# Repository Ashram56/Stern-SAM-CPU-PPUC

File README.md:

# Stern SAM CPU PPUC

A replacement CPU board for the Stern SAM pinball platform. A Raspberry Pi runs the original game ROM under PinMAME
through the [PPUC](https://github.com/PPUC) stack. An RP2354B on the same board drives the original IO power board bus (J1)
with its PIO, reads the switch matrix, dedicated switches and DIP switches, and can scan the original DMD.

- [docs/ARCHITECTURE.md](docs/ARCHITECTURE.md): architecture, bus timing, pin budget, safety, and open questions.
- [docs/reference/](docs/reference/): Stern SAM manual extracts (IO power driver and CPU/Sound board schematics, backbox,
  playfield, cabinet and coin door wiring).

Background:
- [Tron-Legacy-LE-ROM-Decryption/io/bus](https://github.com/Ashram56/Tron-Legacy-LE-ROM-Decryption/tree/main/io/bus):
  the CPU to IO board bus as the SAM ROM drives it.
- [Stern-SAM-Databus-Analysis](https://github.com/Ashram56/Stern-SAM-Databus-Analysis): J1 pinout and IO board schematic notes.

## Licence

- Firmware and software: GNU GPL v3 ([LICENSE](LICENSE)), matching PPUC.
- Hardware design files: CERN Open Hardware Licence v2, strongly reciprocal ([LICENSE-HARDWARE](LICENSE-HARDWARE)).
- The manual extracts in `docs/reference/` are Stern Pinball's material, kept for reference, and are not covered by
  either licence.

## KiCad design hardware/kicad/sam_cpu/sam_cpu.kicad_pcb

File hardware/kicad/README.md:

# SAM CPU replacement board: KiCad project

Draft 0.2 of the schematic, drawn from [`docs/ARCHITECTURE.md`](../../docs/ARCHITECTURE.md). The PCB placement draft is described in [`PCB.md`](PCB.md).
Licence: CERN-OHL-S v2 (see [`LICENSE-HARDWARE`](../../LICENSE-HARDWARE)).

- `sam_cpu/`: the KiCad 10 project (10.0 file format). Open `sam_cpu.kicad_pro` in KiCad 10. All symbols come from
  the standard KiCad 10 libraries and are embedded in the sheets, so no project library is needed.
- `sam_cpu/sam_cpu.pdf`: the sheets exported to PDF, for reading without KiCad.
- `tools/`: the Python scripts that generated this draft (see the end of this file).

## Sheets

Every connection is drawn as a wire. Each connector sits on the same page as the parts that drive or read it.
Signals that go to another page use global labels, and each label shows the page numbers where the signal
continues, in square brackets.

| Page | Sheet | Content | Architecture doc |
|---|---|---|---|
| 2 | Power | J11 (original connector: +5 V, ground, 12 V on pin 6), J17 external +5 V, ideal-diode mux with external priority, J23 external +12 V and J11 pin 6 through an ideal-diode OR (external priority) to the +12 V rail (polyfuse + TVS), TPS54302 buck for the Pi 5 V (a 3-pin header with one shunt picks board +5 V, buck or none for a Jetson), NCP1117 3.3 V (ceramic-stable), +4.5 V switch supply, ADC supply monitors, rail test points | 9.3 |
| 3 | MCU and Pi | RP2354B, crystal, core regulator parts, TPS3808 reset supervisor, RESET / BOOTSEL buttons, status LED, J21 Raspberry Pi 4 40-pin header (UART0, SPI0, I2S, RUN, BOOTSEL, IRQ) (no USB: the Pi flashes the RP2354B over SWD on J21 pins 18 / 22, GPIO24 / GPIO25), U25 DS3231MZ real-time clock on the Pi I2C1 with a CR2032 (BT1) | 4.2, 9.1, 9.2 |
| 4 | IO bus | J9 to IO board J1: SN74LVC8T245 data, 74AHCT541 address + IOSTB, 2N7002 open-drain NBRESET, 33 R series resistor packs | 3.1, 3.2 |
| 5 | Switch columns | 74HC595 + 8 MMBT3904 strobe drivers, J1 switch columns | 5.3, 5.4 |
| 6 | Switch rows 1-8 | J6, 8 returns: diode, 1 k to +4.5 V, 220 R + 100 nF, LM339 against 2.25 V (copy of the original), 74HC165, VREF divider | 5.2, 5.3 |
| 7 | Switch rows 9-16 | J12, same circuit, 74HC165 | 5.2, 5.3 |
| 8 | Dedicated switches 1-16 | J2, J3, input filters, 2 x 74HC165, coin door memory protect | 5.2, 5.3 |
| 9 | Dedicated switches 17-24 | J13, input filters, 74HC165 (DIP block removed) | 5.2, 5.3 |
| 10 | (removed) | GI dimmer sheet removed in the second alternative | 10.2 |
| 11 | Audio | PCM5102A DAC from Pi I2S; U23 TDA7297 bridge amplifier for left / right (J10, J22); (L + R) / 2 110 Hz low-pass (OPA1678) into U24 TDA7297 for the subwoofer (J24); all on +12 V; software mute | 8 |
| 12 | Switch chain extensions | U30 7th 74HC165 (coin door memory protect); U31 extra 74HC595 first in the strobe chain (LED_STATUS, GI_SPARE). File name `dmd_panels.kicad_sch` kept from when the HD panel outputs lived here | 5.3, 9.2 |
| 13 | RS485 and I2S | Isolated RS485 port: ADM2682E (isoPower, 5 kV) with SM712 TVS, JP2 termination jumper and two top-entry RJ45s J27 / J29 on GND_ISO, wired to both the Pi UART3 and the RP2354B UART1 through 1 k; J28 I2S input header for a remote Pi, in parallel with J21; J30 switched 3.5 mm line-in jack between the DAC and the amplifiers | new |

The prototype uses a Raspberry Pi 4 plugged into the 40-pin header J21. The Pi keeps its own HDMI output, so no
high-speed signals are routed on this board. A CM4 is not planned for now.

Connector references follow the original CPU/Sound board 520-5246-00 (J1, J2, J3, J5, J6, J9, J10, J11, J12,
J13), so the cabinet harness labels still match. The harness connectors J1, J2, J3, J6, J12 and J13 use 3.96 mm
KK-396 headers like the original board, so the existing harness plugs fit. New connectors start at J17: J17 external +5 V, J18 GI dimmer,
J19 USB-C to the Pi, J20 SWD, J21 Raspberry Pi header, J22 stereo speaker pairs, J23 external +12 V, J24 subwoofer, J27 / J29 RS485 in / out (RJ45, isolated), J28 I2S input, J30 line-in (3.5 mm).
J5 (original DMD) and J25 / J26 (HD panels) were removed in draft 0.6, so J5 is no longer fitted.

Test points (TP1-TP22, 1.5 mm SMD pads): +5V, +3V3, +4V5, +12V and two GND on the power page; +1V1, RUN and
GND by the RP2354B; J9 IOSTB, NBRESET, D0 and A0 on the bus; strobes 1-2, SW_CLK and SW_DATA on the switch columns
page; VREF; DAC left / right outputs, subwoofer filter output and GND on the audio page.

## RP2354B GPIO map (draft 0.6)

| GPIO | Signal |
|---|---|
| 0-19 | unchanged (GPIO17 = SW_LOAD_N, now also the 74HC595 latch) |
| 20-22 | RP_RS485_TX, RP_RS485_RX (UART1), RP_RS485_DE: the RS485 port when the Pi is remote |
| 23-36 | unassigned (no-connect flags; were the DMD outputs) |
| 37 | RP_IRQ_N |
| 35 | AMP_PDN (low = TAS5805M shutdown / reset; input = run, R190 pull-up) |
| 38-39 | AMP_SDA, AMP_SCL (I2C1 to the two TAS5805M, 0x2C / 0x2D; GPIO39 was AMP_MUTE) |
| 40-42 | FRAME_MOSI, FRAME_CS_N, FRAME_SCK (SPI1, frames from the Pi) |
| 43 | spare |
| 44-45 | RP_UART_TX / RX (UART0 to the Pi) |
| 46-47 | VMON_5V, VMON_12V |

The switch input chain is now 7 x 74HC165 (56 bits, U30 last, holding the coin door memory protect) and the strobe
chain 3 x 74HC595 with U31 first (QA LED_STATUS, QB GI_SPARE).

## DMD removed, RS485 and I2S added (draft 0.6, 2026-10-07)

Both DMD interfaces are gone (Vincent: DMD signals will not survive the long wires in the cabinet): the original
DMD driver (J5, U21, RN4, RN5, R176-R182, C95) and the HD panel bus (J25, J26, U27-U29, RN6-RN11, C122-C124, TP23,
TP24). The display is left to the Pi.

The new RS485 port (J27, RJ45) serves the two ways the Pi can be fitted:

| Pi | RS485 port belongs to | Pins |
|---|---|---|
| On J21 | Pi UART3 | J21 pin 7 GPIO4 TXD3, pin 29 GPIO5 RXD3, pin 26 GPIO7 RTS3 = driver enable (Linux RS485 mode) |
| Remote | RP2354B UART1 | GPIO20 TX, GPIO21 RX, GPIO22 driver enable; the remote Pi's I2S comes in on J28 |

Both sides reach the transceiver through 1 k resistors and the transceiver stays in receive (10 k pull-down on
DE / RE) until one side drives. Only the side that is configured drives; the other keeps its pins as inputs, which
is how both boot. RJ45 pinout (DMX-over-RJ45 order): pin 1 A, pin 2 B, pins 7 / 8 GND, pins 3-6 not connected.
JP2 fits the 120 R termination (fit it only at an end of the line). J28 (2x3, 2.54 mm): 1 I2S_BCK, 3 I2S_LRCK,
5 I2S_DIN, even pins GND. I2S is clocked logic too, so keep that cable short.

Draft 0.7 (same day, Vincent's review): the transceiver is now the isolated ADM2682E, like Stern's node boards. The
whole cable side (A / B, the SM712, the termination, RJ45 pins 7 / 8) is on GND_ISO, powered by the chip's own
isoPower converter, with its own copper zone 2 mm clear of GND. Two top-entry RJ45s in parallel: J27 in, J29 out
(J29 can be left unfitted). J30 is a switched 3.5 mm stereo jack for the Pi 4's headphone output: with no plug the
PCM5102A drives the amplifiers through the jack's normally-closed tip / ring contacts (nets AUD_DAC_L / R to
AUD_AMP_L / R); a plug disconnects the DAC. The amplifier input dividers were sized for the DAC's 2.1 Vrms, so the
Pi's lower analog level plays quieter.

## Audio option B: TAS5805M (2026-11-12)

The analog chain (PCM5102A, OPA1678, two TDA7297) is replaced by two TI TAS5805M class D amplifiers with I2S input
and an internal DSP (c62 schematic, c63 placement, c64 / c65 and the hand routing on this branch). U23 drives the
left / right speakers (J10, J22), U24 the subwoofer (J24); both on +12 V, 4 or 8 ohm speakers.

- **I2C only to the RP2354B**: GPIO38 AMP_SDA, GPIO39 AMP_SCL (pull-ups R188 / R189), addresses 0x2C (U23) and
  0x2D (U24). The firmware loads the DSP coefficients (equalizer, crossover) at boot and can change them later.
- **PDN** (c64, c66): R190 10 k pull-up to +3V3 and C158 100 nF, plus GPIO35 (Vincent's choice, 2026-11-12). With
  GPIO35 as an input the amplifiers leave shutdown 1 ms after power up; GPIO35 low is a hard reset / shutdown (use it if
  the I2C bus locks up). The firmware also resets over I2C (register 0x01) and mutes with deep sleep / Hi-Z through
  register 0x03 (DEVICE_CTRL2). The route runs on In2 for 26 mm under slow nets only. GPIO36 stays free.
- **Line in** (no Pi fitted, external mini PC): J30's plug switch LINE_DET drives only U26 (74HC157). With a plug,
  U26 passes the PCM1808 ADC (U22, master, Y2 12.288 MHz) instead of the Pi / J28 I2S. The TAS5805M mutes by itself
  when its I2S clocks change. LINE_DET is not wired to the RP2354B; the firmware can read the amplifiers' clock status over I2C.
- **Mux channel order** (c65): A/B1 = LRCK, A/B2 = BCK, A/B3 = DIN (so the ADC clocks do not cross under U26).

- **Review of the stage** (2026-11-12, on b560bbc): the +12 V feed of the amplifiers is now a ring on B.Cu (new
  1.2 mm link at y 100.37 between the x 115.2 trunk and the x 130.4 trunk; the x 115.2 trunk is 1.5 mm), so U24 is
  15 mm from the feed instead of 85 mm. The three I2S tracks change layer west of C120 to let the link pass. Output
  tracks between the pins and the bootstrap capacitors are 0.6 to 0.8 mm (0.4 mm only in the pin escape), each
  22 uF has two ground vias, the four SPK / SUB vias at the inductors are joined at their centre. The U24 DVDD
  capacitor is now **C159**: it had taken the reference C119 of the DS3231 decoupling capacitor (MCU sheet), which
  had disappeared from the board and is back at (72.0, 133.4). Open points (not changed): I2S inputs of U26 float
  without a Pi, LINE_DET goes straight from the jack contact to U26, 0.2 mm thermal vias in the TAS5805M footprint,
  0.5 mm courtyard gaps in the audio block, no voltage / part number fields on the audio parts.

- **Footprint** (c67b, 2026-11-12, checked against the TAS5805M data sheet SLASEH5D, package PWP0028M): U23 / U24
  use `TSSOP-28-1EP_4.4x9.7mm_P0.65mm_EP3.4x9.7mm_Mask3.1x4.05mm_ThermalVias` (the KiCad footprint drawn from this
  data sheet) instead of the PWP0028V one (LM5176, 2.94 x 5.62 mm mask opening, longer than the 4.05 mm thermal pad
  of this package). Thermal vias stay at 0.2 mm drill, 1.2 mm pitch, as TI draws them, and connect to the planes
  without thermal relief (section 9.1.3.2.1).

- **Use without a Pi and spacing** (c67, Vincent 2026-11-12): R199 / R200 / R201 100k pull I2S_BCK / I2S_LRCK /
  I2S_DIN to GND (U26 inputs no longer float), R202 10k + C160 100 nF between LINE_DET and the U26 select pin (new
  net MUX_SEL). On the board the five new parts and C146 to C153, FB4, R198 were placed by hand with 1.5 mm between
  courtyards (4 mm to connectors): FB4 / C147 west of U22, C148 / C152 above it, C151 / C150 / R198 east, C160 and
  R202 west of U26, C146 south of U26, C153 south of Y2, pull-downs and C149 in a row at y 123.5. ADC_VCC, ADC_VREF,
  LINE_DET and MUX_SEL were re-routed by hand. The decoupling and bootstrap capacitors against the TAS5805M stay at
  0.5 mm on purpose (data sheet 9.1.2). C150 (VDD) and C153 (Y2) reach their pins through the +3V3 plane.

- **Track cleanup over the whole board** (c68, 2026-11-12, asked by Vincent after an odd hook on LINE_DET): 78
  segments lying under another one removed, about 120 staircases and small detours straightened (same corridor, no
  via added or moved), the 14 acute corners and 27 double-backs removed, 10 segments off 45 degrees redrawn, the
  EXT_12V snake between R213 and U33 replaced by four segments. 5677 segments before, 5261 after. Left as they are:
  7 segments off 45 degrees by less than 0.03 mm (vias that are off the grid), about 230 segments under 0.1 mm
  inside pads and vias, 90 degree corners, and the long routes of the lamp matrix and bus areas, which go round
  real obstacles. Scripts: `tools/changes/c68_track_cleanup/`.

- **Vias and layer changes** (c69, 2026-11-12, asked by Vincent): the LINE_DET via now sits level with R198.2;
  EXT_12V to R213 is 0.3 mm (divider only) with its via in line; J11_5V no longer hops to the front and back
  through two vias next to TP1; 30 vias that a track reached and left at less than 90 degrees were slid along
  their track; 18 chains that changed layer for no reason stay on one layer. 1187 vias before, 1157 after, 5060
  segments. Left: 68 vias of the same kind that are held by their neighbours (mostly IC fan-outs whose via is on
  the outer side of the pad row), and the J11_5V loop from U1.6 to JP1.2 round x 110.5, which needs the two B.Cu
  tracks at y 107.3 and y 108.2 moved first. Scripts: `tools/changes/c69_via_cleanup/`.

- **J11 5 V input, U1.6 to JP1.2** (c70, Vincent 2026-11-12): this link carries the whole +5V load when the board
  is fed from J11 (up to 3 A with the Pi on JP3 1-2). The 34 mm, 0.5 mm loop round x 110.5 (about 35 mOhm, four
  vias) is replaced by 4.5 mm: 0.3 mm from the pin to the via at (99.5, 105.44), 0.8 mm on B.Cu under the +5V
  track to a new 0.8 / 0.4 via at (99.92, 107.75), 0.8 mm on F.Cu into JP1.2 (about 6 mOhm). To open the way on
  B.Cu, +4V5 dips to y 108.475 between x 98.4 and x 101.7 and the J11 pin 1 feed to FB1 runs at y 109.25
  (Power_HI clearance 0.25 mm). Script: `tools/changes/c69_via_cleanup/c70_j11_5v.py`.

## Checks

- ERC (KiCad 10.0.6, `kicad-cli sch erc`): 0 errors, 0 warnings (draft 0.6).
- The netlist KiCad exports was compared pin by pin with the nets the generator intended (`tools/verify2.py`):
  1339 pins, 313 nets, no differences.

## Open items before layout

- **Power mux**: the doc names a TPS2121; the board uses a TI TPS2117 (same family, 4 A, stocked at JLCPCB) in
  priority mode: external +5 V (J17) on VIN1 while it is above about 4 V (R1 / R2 on PR1), else J11.
- **RP2354B support parts** were checked against the RP2350 hardware design guide: 3.3 uH Abracon
  AOTA-B201610S3R3-101-T for L1 (mind its polarity dot), 4.7 uF on VREG_VIN and on the 1.1 V output, 33 R + 4.7 uF
  on VREG_AVDD, ABM8-272-T3 12 MHz crystal with 15 pF and 1 k, 27 R USB series resistors, 100 nF per supply pin.
  The guide uses 0402; this board uses 0603 for 100 nF and 0805 / 1206 for every regulator capacitor so their value
  holds under DC bias.
- **Audio**: TDA7297 outputs are bridged, so no speaker wire may touch ground. J10 pins 3 / 4 (ground on the
  original board) now carry left - / right -: check the harness keeps the two speaker returns separate. At 12 V
  expect about 6 W per bridge into 8 ohm (the TDA7297 is rated 2 x 15 W at 18 V / 8 ohm); check the speaker
  impedances before using 4 ohm. U23 and U24 need a heatsink (keep-out drawn on the board). The datasheet pin list
  was not reachable from here: confirm pins 1 / 2 and 14 / 15 output polarity (symbol: pin 1 and pin 15 = +).
- **Pin orders to confirm with a meter** on a real board or harness: J6 / J12 return order, J2 / J3 / J13 dedicated
  input order, J1 strobe order.
- **Memory protect**: J2 pin 10 (coin door) is now read through U30, the 7th 74HC165.
- **Audio gain** and **LM339 / switch filter values** are starting points for the bench.
- **Part numbers**: footprints are JLCPCB-friendly packages (0603 passives, SOIC / TSSOP logic, SOT-23), but no LCSC
  numbers are filled in yet. They come with the BOM for layout.

## How the draft was generated

`tools/design2.py` describes the parts, their nets and their placement on each page. `tools/build2.py` places the
symbols from the KiCad library, routes the wires on the 1.27 mm grid (`tools/sch.py`), adds power symbols and global
labels, and writes the sheets in the KiCad 9 format, which `kicad-cli sch upgrade` then converts to KiCad 10.
`tools/verify2.py` compares KiCad's exported netlist with the intended nets. `tools/run.sh` does all of it, plus ERC
and the PDF export:

```
KICAD_CLI=kicad-cli KICAD9_SYMBOL_DIR=/usr/share/kicad/symbols tools/run.sh /tmp/out
```

From now on the `.kicad_sch` files are the source of truth. Edit them in KiCad; do not regenerate over them.

### Incremental changes

Since the two-panel DMD change, the sheets and the board are edited in place, never regenerated. The scripts in
`tools/changes/` (c01-c04) are the record of each edit: GPIO remap on the MCU sheet, net renames, the new DMD
panels sheet, and the board update (pad nets plus the 20 new footprints; no existing footprint moved). Draft 0.6:
`c11_remove_dmd.py` (DMD parts out of pages 10 and 12, no-connect flags on GPIO20-36), `c13_rs485_i2s_sheet.py`
(new page 13), `c14_mcu_rs485_labels.py` (RS485 labels on the RP2354B and J21), and on the board
`c12_board_remove_dmd.py` and `c15_board_rs485_i2s.py`. Draft 0.7: `c16_rs485_isolated_sheet.py` (page 13 rewritten:
ADM2682E, J29, J30), `c17_audio_line_in.py` (DAC output wires split for J30) and `c18_board_isolated_rs485.py`
(extension, MH3, placement, GND_ISO zone), then `c19_board_taller.py` (bottom edge 5 mm lower so MH3 is a
complete keyhole), `c20_line_in_near_amps.py` (J30 next to the amplifiers), `c21_bus_buffer_channels.py` (U6 / U7
channel order reversed on the IO bus sheet) and `c22_board_rp_fanout.py` (U6 / U7 turned, R13 / R14 swapped, RS485
resistors next to U4). They are not
idempotent: each one was run once on the previous state.

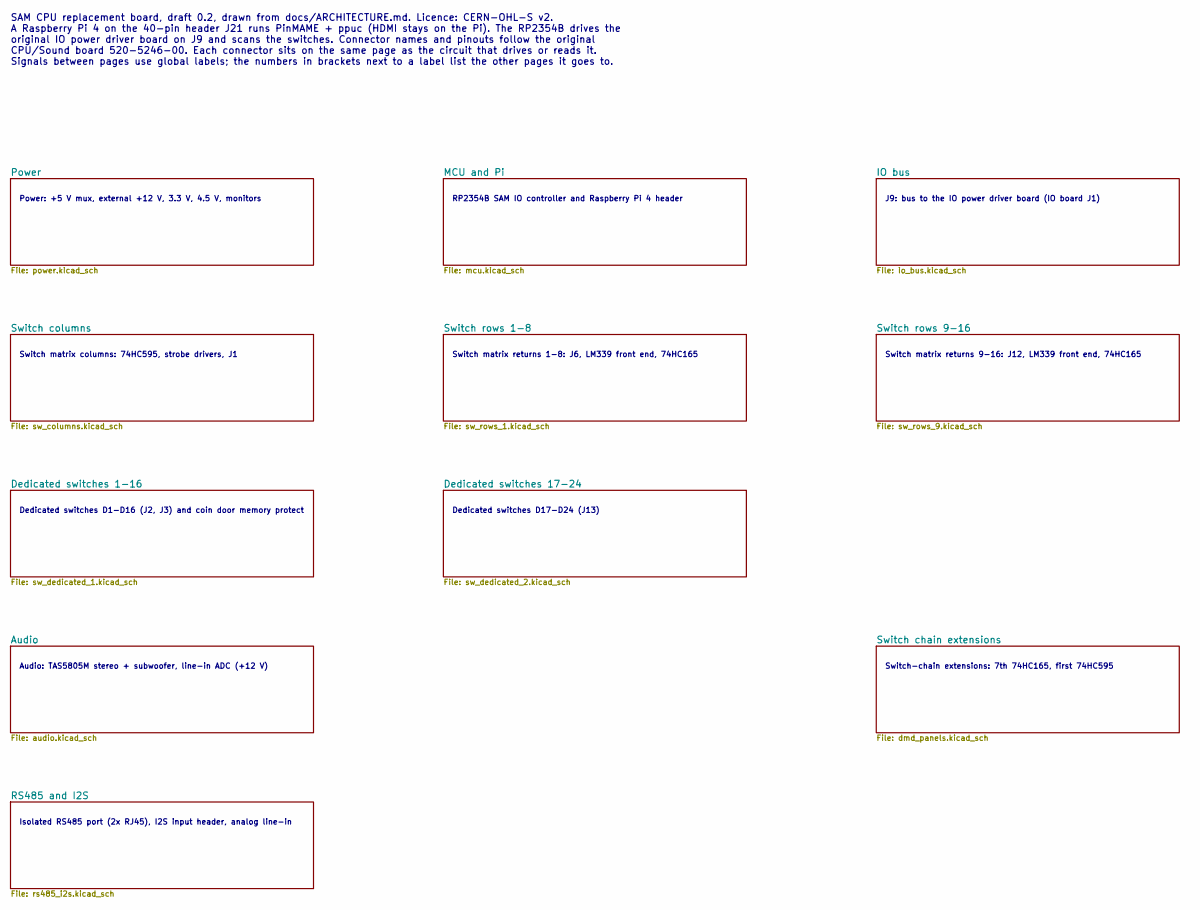
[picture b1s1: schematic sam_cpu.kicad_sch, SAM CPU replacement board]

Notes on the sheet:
Dedicated switches D17-D24 (J13)
Power: +5 V mux, external +12 V, 3.3 V, 4.5 V, monitors
Dedicated switches D1-D16 (J2, J3) and coin door memory protect
J9: bus to the IO power driver board (IO board J1)
SAM CPU replacement board, draft 0.2, drawn from docs/ARCHITECTURE.md. Licence: CERN-OHL-S v2. A Raspberry Pi 4 on the 40-pin header J21 runs PinMAME + ppuc (HDMI stays on the Pi). The RP2354B drives the original IO power driver board on J9 and scans the switches. Connector names and pinouts follow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
Switch matrix columns: 74HC595, strobe drivers, J1
Switch matrix returns 1-8: J6, LM339 front end, 74HC165
Audio: TAS5805M stereo + subwoofer, line-in ADC (+12 V)
Isolated RS485 port (2x RJ45), I2S input header, analog line-in
Switch-chain extensions: 7th 74HC165, first 74HC595
Switch matrix returns 9-16: J12, LM339 front end, 74HC165
RP2354B SAM IO controller and Raspberry Pi 4 header

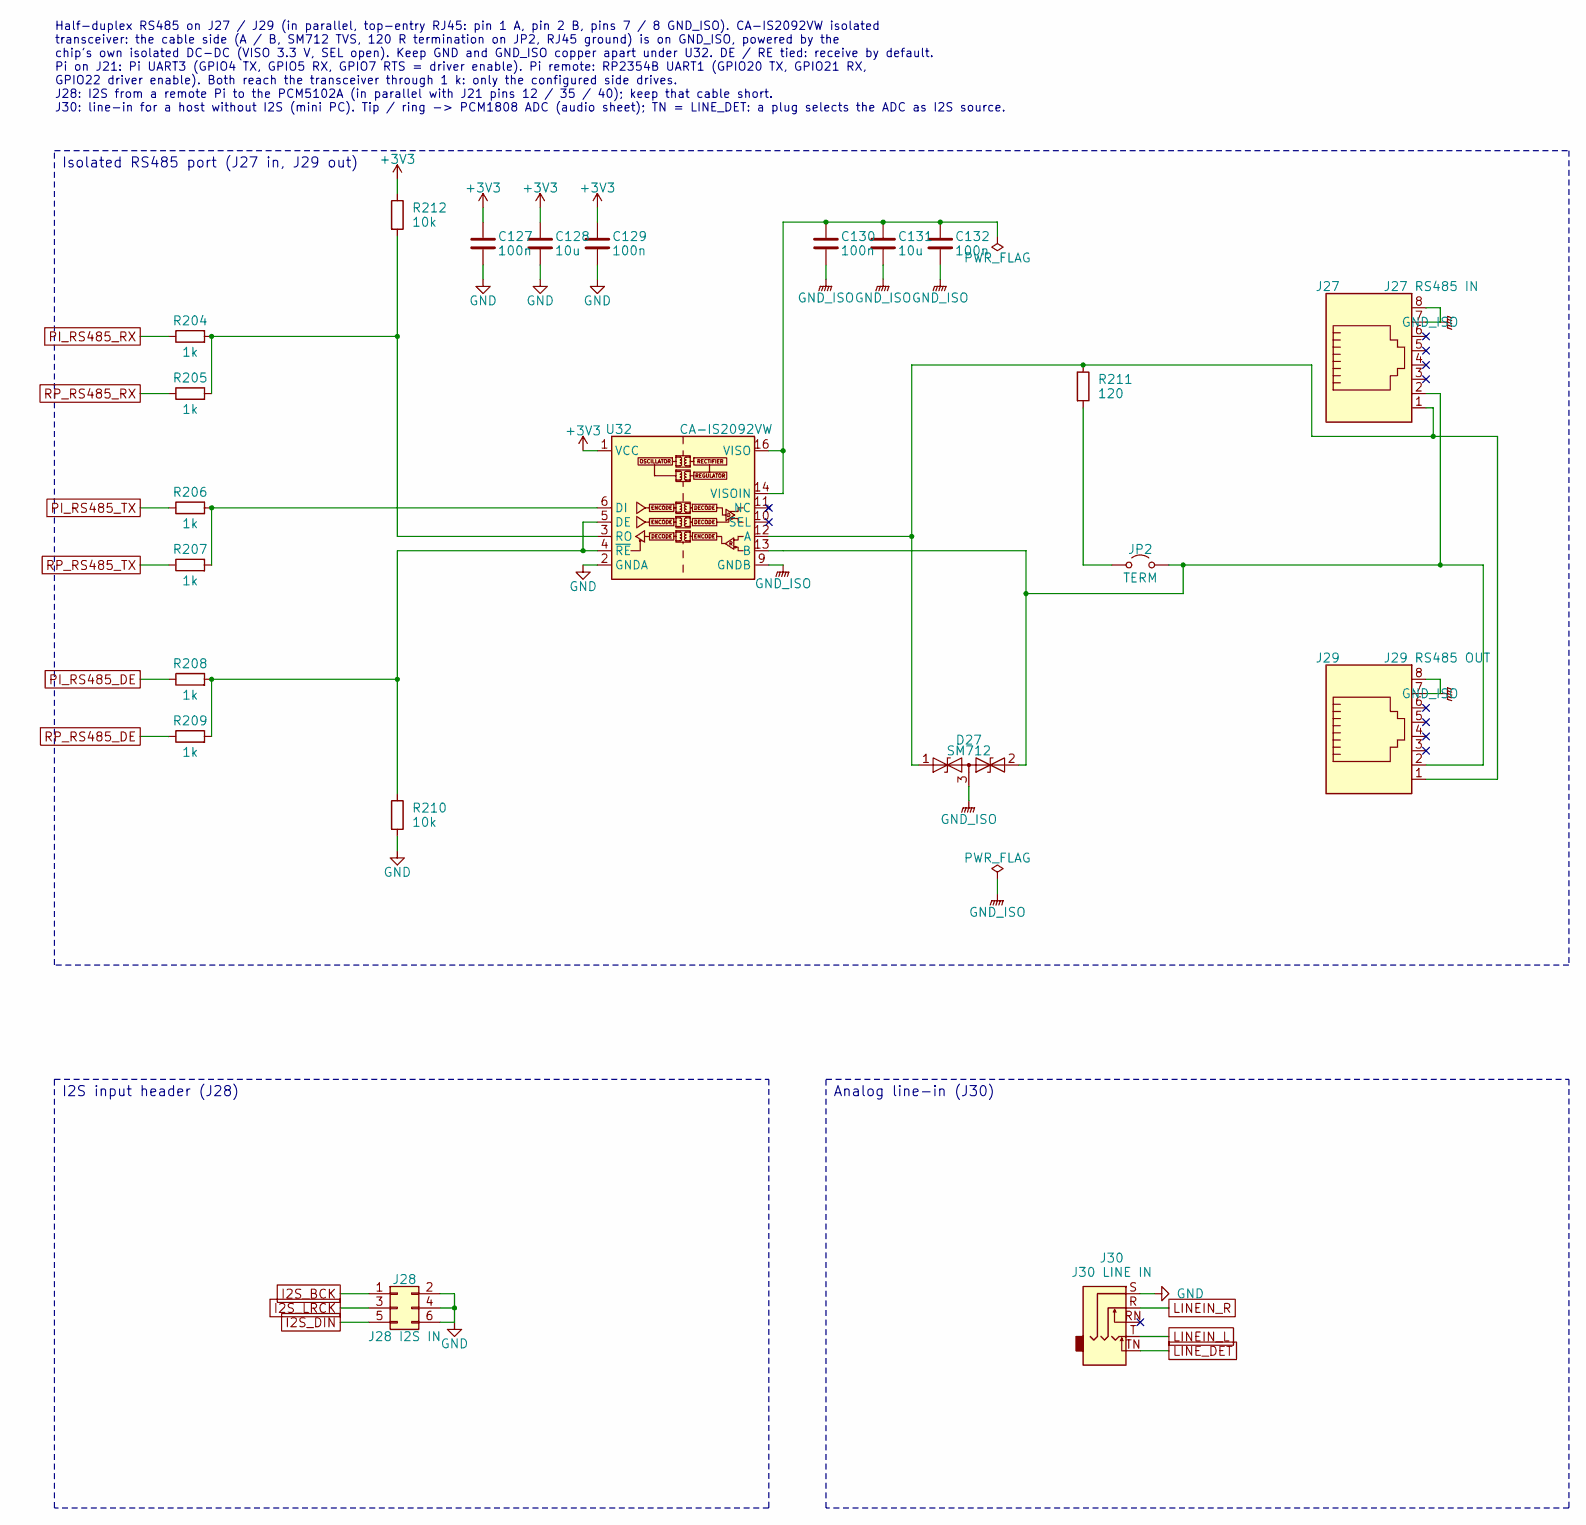
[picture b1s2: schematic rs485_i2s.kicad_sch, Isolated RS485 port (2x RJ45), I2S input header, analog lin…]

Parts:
C127, C130: 100n; C_0603_1608Metric
C128, C131: 10u; C_0805_2012Metric
C129, C132: 100n; C_0805_2012Metric
D27: SM712; SOT-23
J27: J27 RS485 IN; RJ45_Connfly_DS1128-05-S8B8P_Horizontal
J28: J28 I2S IN; PinHeader_2x03_P2.54mm_Vertical
J29: J29 RS485 OUT; RJ45_Connfly_DS1128-05-S8B8P_Horizontal
J30: J30 LINE IN; Jack_3.5mm_PJ-393-7A_Horizontal
JP2: TERM; PinHeader_1x02_P2.54mm_Vertical
R204, R205: 1k; R_0603_1608Metric
R206, R207, R208, R209: 1k; R_0805_2012Metric
R210: 10k; R_0805_2012Metric
R211: 120; R_1206_3216Metric
R212: 10k; R_0603_1608Metric
U32: CA-IS2092VW; SOIC-16W_7.5x12.8mm_P1.27mm

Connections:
+3V3: C127.1, C128.1, C129.1, R212.1, U32.1 (VCC), U32.7 (VCCL); also elsewhere on the board
GND: C127.2, C128.2, C129.2, J28.2, J28.4, J28.6, J30.S, R210.2, U32.2 (GNDA), U32.8 (GNDA); also elsewhere on the board
GND_ISO: C130.2, C131.2, C132.2, D27.3 (common), J27.7, J27.8, J29.7, J29.8, U32.9 (GNDB), U32.15 (GNDB)
I2S_BCK: J28.1; also elsewhere on the board
I2S_DIN: J28.5; also elsewhere on the board
I2S_LRCK: J28.3; also elsewhere on the board
LINEIN_L: J30.T; also elsewhere on the board
LINEIN_R: J30.R; also elsewhere on the board
LINE_DET: J30.TN; also elsewhere on the board
unnamed: D27.1 (A1), J27.1, J29.1, R211.1, U32.12 (A)
unnamed: D27.2 (A2), J27.2, J29.2, JP2.2 (B), U32.13 (B)
unnamed: JP2.1 (A), R211.2
unnamed: R208.2, R209.2, R210.1, U32.4 (~RE), U32.5 (DE)
unnamed: R206.2, R207.2, U32.6 (DI)
unnamed: R204.2, R205.2, R212.2, U32.3 (RO)
unnamed: C130.1, C131.1, C132.1, U32.14 (VISOIN), U32.16 (VISO)
PI_RS485_DE: R208.1; also elsewhere on the board
PI_RS485_RX: R204.1; also elsewhere on the board
PI_RS485_TX: R206.1; also elsewhere on the board
RP_RS485_DE: R209.1; also elsewhere on the board
RP_RS485_RX: R205.1; also elsewhere on the board
RP_RS485_TX: R207.1; also elsewhere on the board

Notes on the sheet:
Isolated RS485 port (J27 in, J29 out)
I2S input header (J28)
Analog line-in (J30)
Half-duplex RS485 on J27 / J29 (in parallel, top-entry RJ45: pin 1 A, pin 2 B, pins 7 / 8 GND_ISO). CA-IS2092VW isolated transceiver: the cable side (A / B, SM712 TVS, 120 R termination on JP2, RJ45 ground) is on GND_ISO, powered by the chip's own isolated DC-DC (VISO 3.3 V, SEL open). Keep GND and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

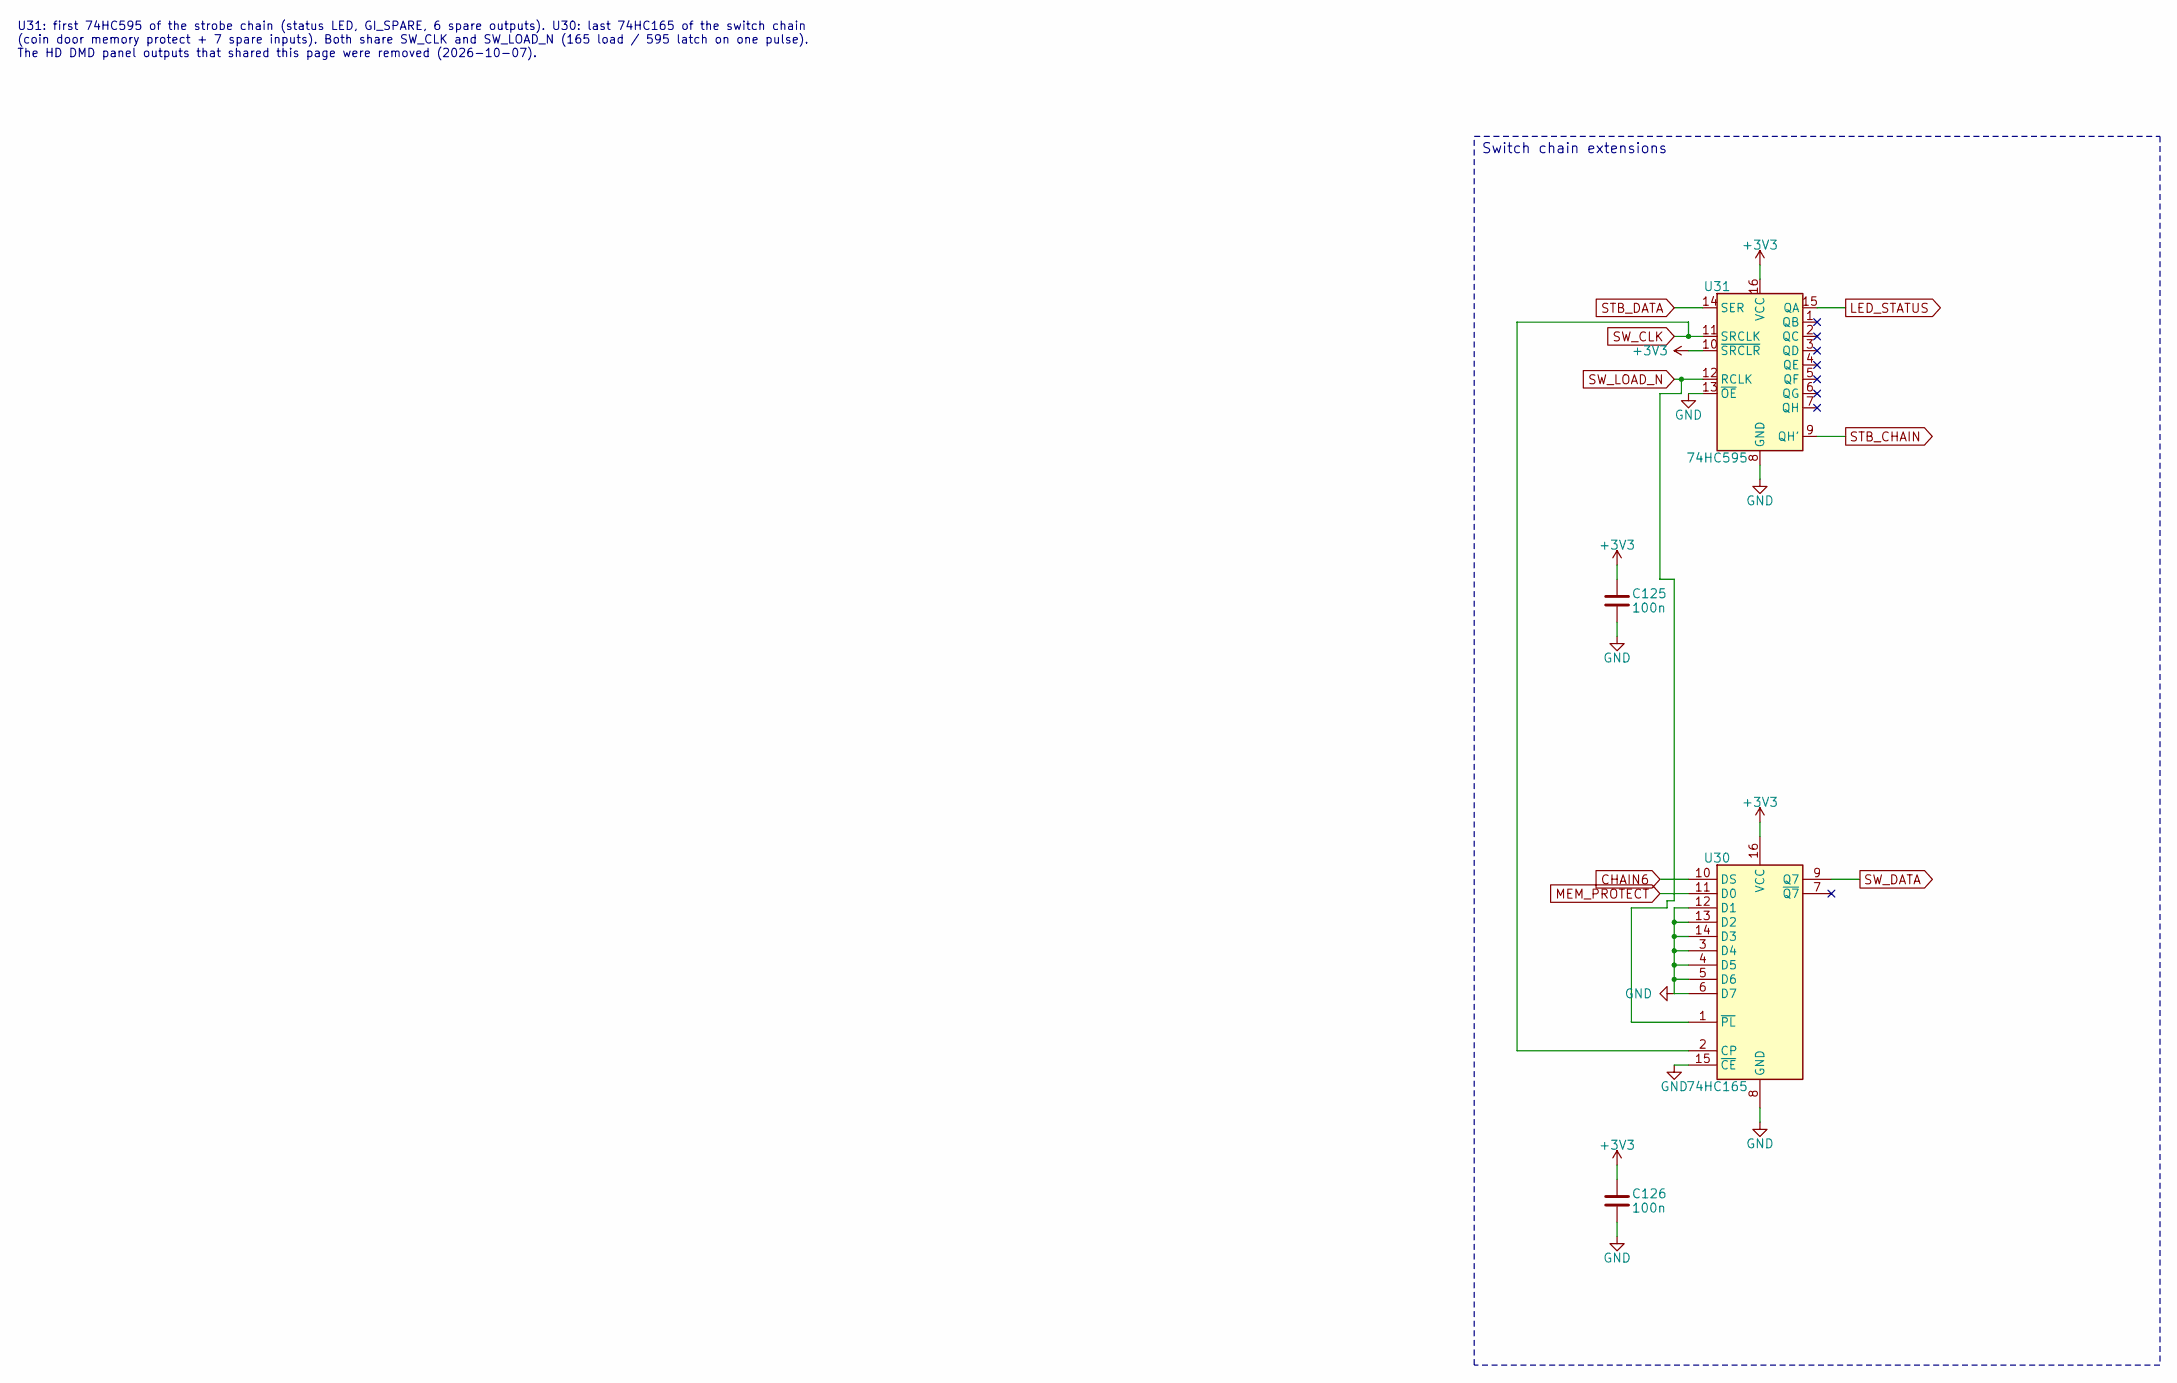
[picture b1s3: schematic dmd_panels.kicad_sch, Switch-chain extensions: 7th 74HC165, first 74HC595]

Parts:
C125, C126: 100n; C_0805_2012Metric
U30: 74HC165; SOIC-16_3.9x9.9mm_P1.27mm
U31: 74HC595; SOIC-16_3.9x9.9mm_P1.27mm

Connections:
+3V3: C125.1, C126.1, U30.16 (VCC), U31.10 (~SRCLR), U31.16 (VCC); also elsewhere on the board
CHAIN6: U30.10 (DS); also elsewhere on the board
GND: C125.2, C126.2, U30.3 (D4), U30.4 (D5), U30.5 (D6), U30.6 (D7), U30.8 (GND), U30.12 (D1), U30.13 (D2), U30.14 (D3), U30.15 (~CE), U31.8 (GND), U31.13 (~OE); also elsewhere on the board
LED_STATUS: U31.15 (QA); also elsewhere on the board
MEM_PROTECT: U30.11 (D0); also elsewhere on the board
STB_CHAIN: U31.9 (QH'); also elsewhere on the board
STB_DATA: U31.14 (SER); also elsewhere on the board
SW_CLK: U30.2 (CP), U31.11 (SRCLK); also elsewhere on the board
SW_DATA: U30.9 (Q7); also elsewhere on the board
SW_LOAD_N: U30.1 (~PL), U31.12 (RCLK); also elsewhere on the board

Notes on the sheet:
Switch chain extensions
U31: first 74HC595 of the strobe chain (status LED, GI_SPARE, 6 spare outputs). U30: last 74HC165 of the switch chain (coin door memory protect + 7 spare inputs). Both share SW_CLK and SW_LOAD_N (165 load / 595 latch on one pulse). The HD DMD panel outputs that shared this page were removed (2026-1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

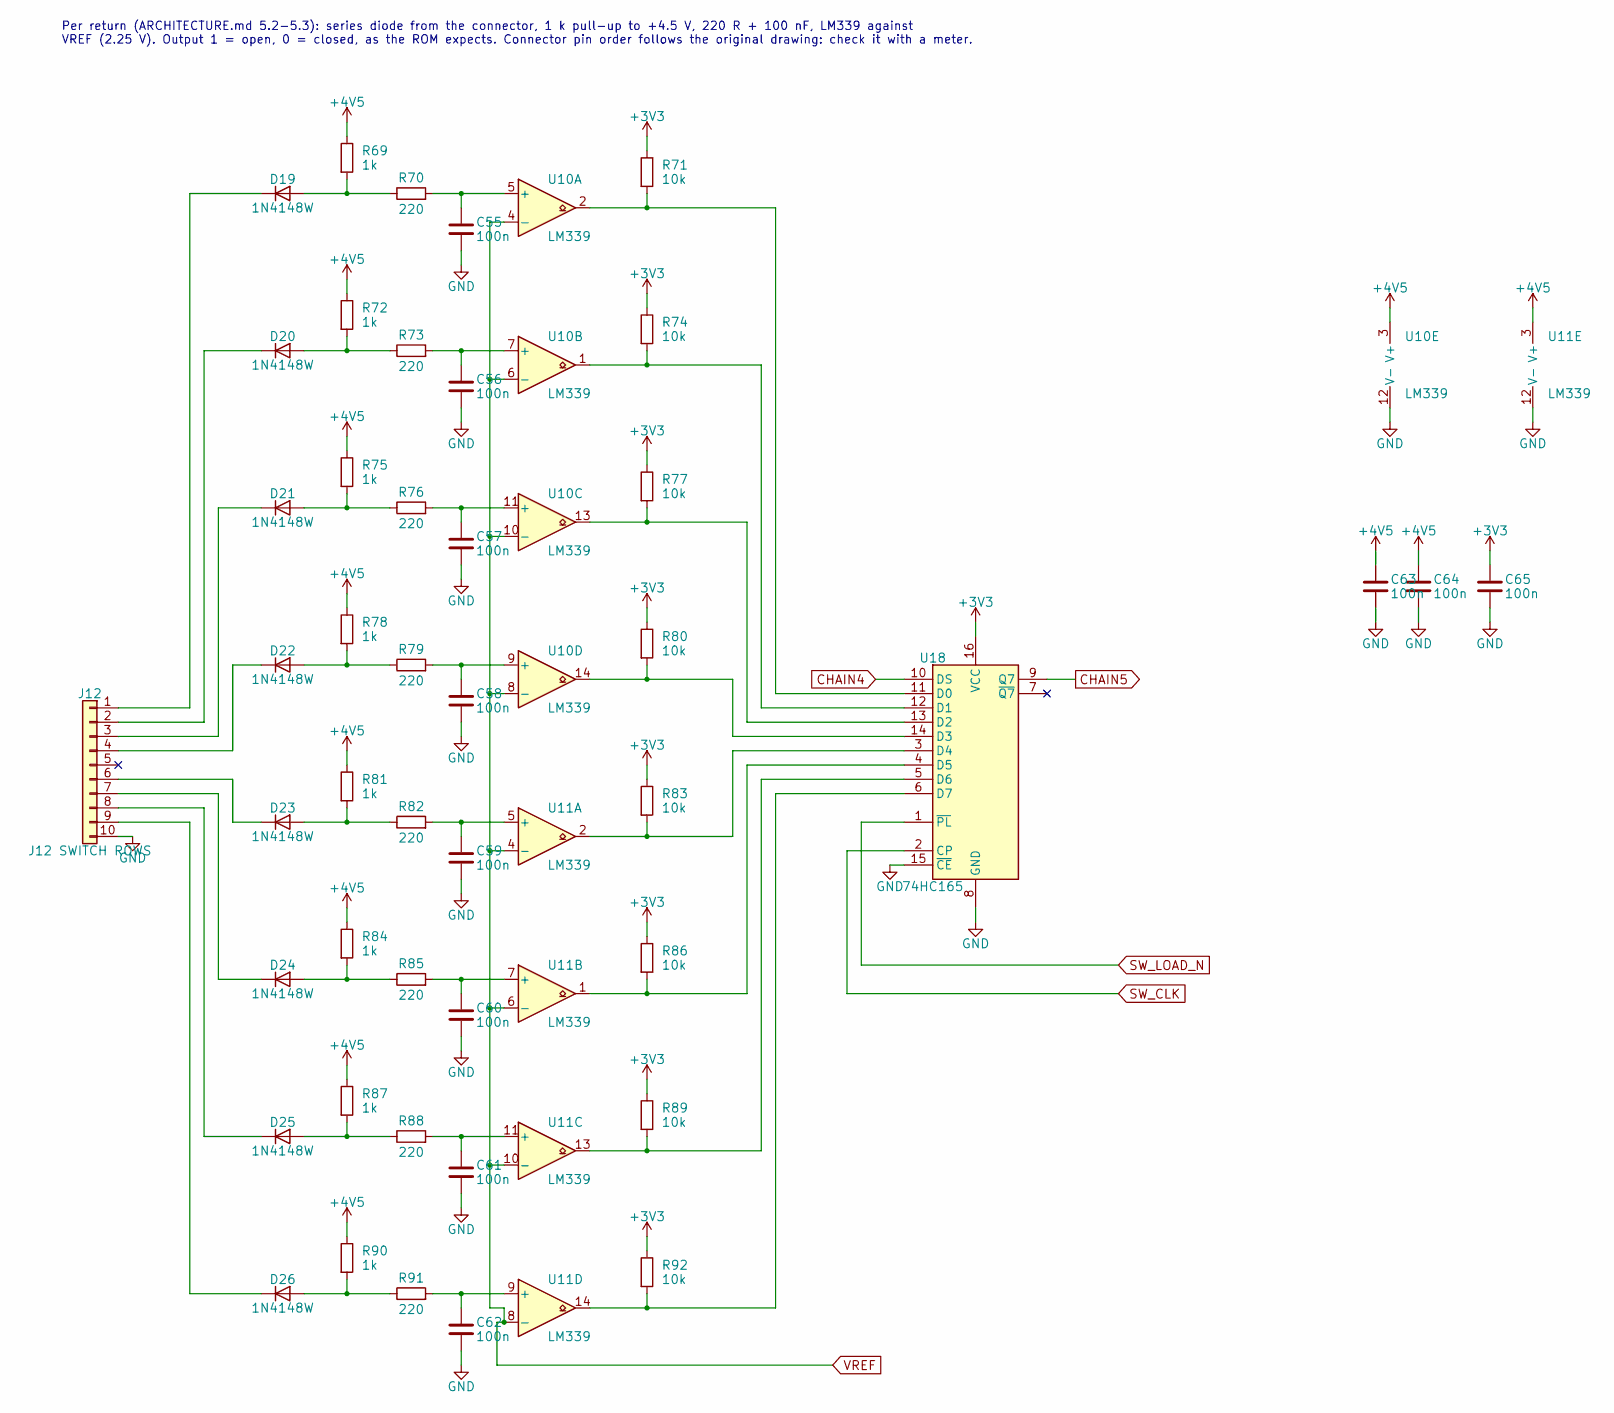
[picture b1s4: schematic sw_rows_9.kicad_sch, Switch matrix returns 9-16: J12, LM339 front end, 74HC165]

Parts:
C55, C56, C57, C58, C59, C60, C61, C62, C64: 100n; C_0603_1608Metric
C63, C65: 100n; C_0805_2012Metric
D19, D20, D21, D22, D23, D24, D25, D26: 1N4148W; D_SOD-123
J12: J12 SWITCH ROWS; Molex_KK-396_A-41791-0010_1x10_P3.96mm_Vertical
R69, R72, R75, R78, R81, R84: 1k; R_0603_1608Metric
R70, R73, R76, R79, R82, R85: 220; R_0603_1608Metric
R71, R74, R77, R80, R86: 10k; R_0603_1608Metric
R83, R89, R92: 10k; R_0805_2012Metric
R87, R90: 1k; R_0805_2012Metric
R88, R91: 220; R_0805_2012Metric
U10, U11: LM339; SOIC-14_3.9x8.7mm_P1.27mm
U18: 74HC165; SOIC-16_3.9x9.9mm_P1.27mm

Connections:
+3V3: C65.1, R71.1, R74.1, R77.1, R80.1, R83.1, R86.1, R89.1, R92.1, U18.16 (VCC); also elsewhere on the board
+4V5: C63.1, C64.1, R69.1, R72.1, R75.1, R78.1, R81.1, R84.1, R87.1, R90.1, U10.3 (V+), U11.3 (V+); also elsewhere on the board
CHAIN4: U18.10 (DS); also elsewhere on the board
CHAIN5: U18.9 (Q7); also elsewhere on the board
GND: C55.2, C56.2, C57.2, C58.2, C59.2, C60.2, C61.2, C62.2, C63.2, C64.2, C65.2, J12.10, U10.12 (V-), U11.12 (V-), U18.8 (GND), U18.15 (~CE); also elsewhere on the board
unnamed: D19.2 (A), R69.2, R70.1
unnamed: D19.1 (K), J12.1
unnamed: D20.2 (A), R72.2, R73.1
unnamed: D20.1 (K), J12.2
unnamed: D21.2 (A), R75.2, R76.1
unnamed: D21.1 (K), J12.3
unnamed: D22.2 (A), R78.2, R79.1
unnamed: D22.1 (K), J12.4
unnamed: D23.2 (A), R81.2, R82.1
unnamed: D23.1 (K), J12.6
unnamed: D24.2 (A), R84.2, R85.1
unnamed: D24.1 (K), J12.7
unnamed: D25.2 (A), R87.2, R88.1
unnamed: D25.1 (K), J12.8
unnamed: D26.2 (A), R90.2, R91.1
unnamed: D26.1 (K), J12.9
unnamed: C55.1, R70.2, U10.5 (+)
unnamed: C56.1, R73.2, U10.7 (+)
unnamed: C57.1, R76.2, U10.11 (+)
unnamed: C58.1, R79.2, U10.9 (+)
unnamed: C59.1, R82.2, U11.5 (+)
unnamed: C60.1, R85.2, U11.7 (+)
unnamed: C61.1, R88.2, U11.11 (+)
unnamed: C62.1, R91.2, U11.9 (+)
unnamed: R71.2, U10.2, U18.11 (D0)
unnamed: R74.2, U10.1, U18.12 (D1)
unnamed: R77.2, U10.13, U18.13 (D2)
unnamed: R80.2, U10.14, U18.14 (D3)
unnamed: R83.2, U11.2, U18.3 (D4)
unnamed: R86.2, U11.1, U18.4 (D5)
unnamed: R89.2, U11.13, U18.5 (D6)
unnamed: R92.2, U11.14, U18.6 (D7)
SW_CLK: U18.2 (CP); also elsewhere on the board
SW_LOAD_N: U18.1 (~PL); also elsewhere on the board
VREF: U10.4 (-), U10.6 (-), U10.8 (-), U10.10 (-), U11.4 (-), U11.6 (-), U11.8 (-), U11.10 (-); also elsewhere on the board

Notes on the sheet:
Per return (ARCHITECTURE.md 5.2-5.3): series diode from the connector, 1 k pull-up to +4.5 V, 220 R + 100 nF, LM339 against VREF (2.25 V). Output 1 = open, 0 = closed, as the ROM expects. Connector pin order follows the original drawing: check it with a meter.

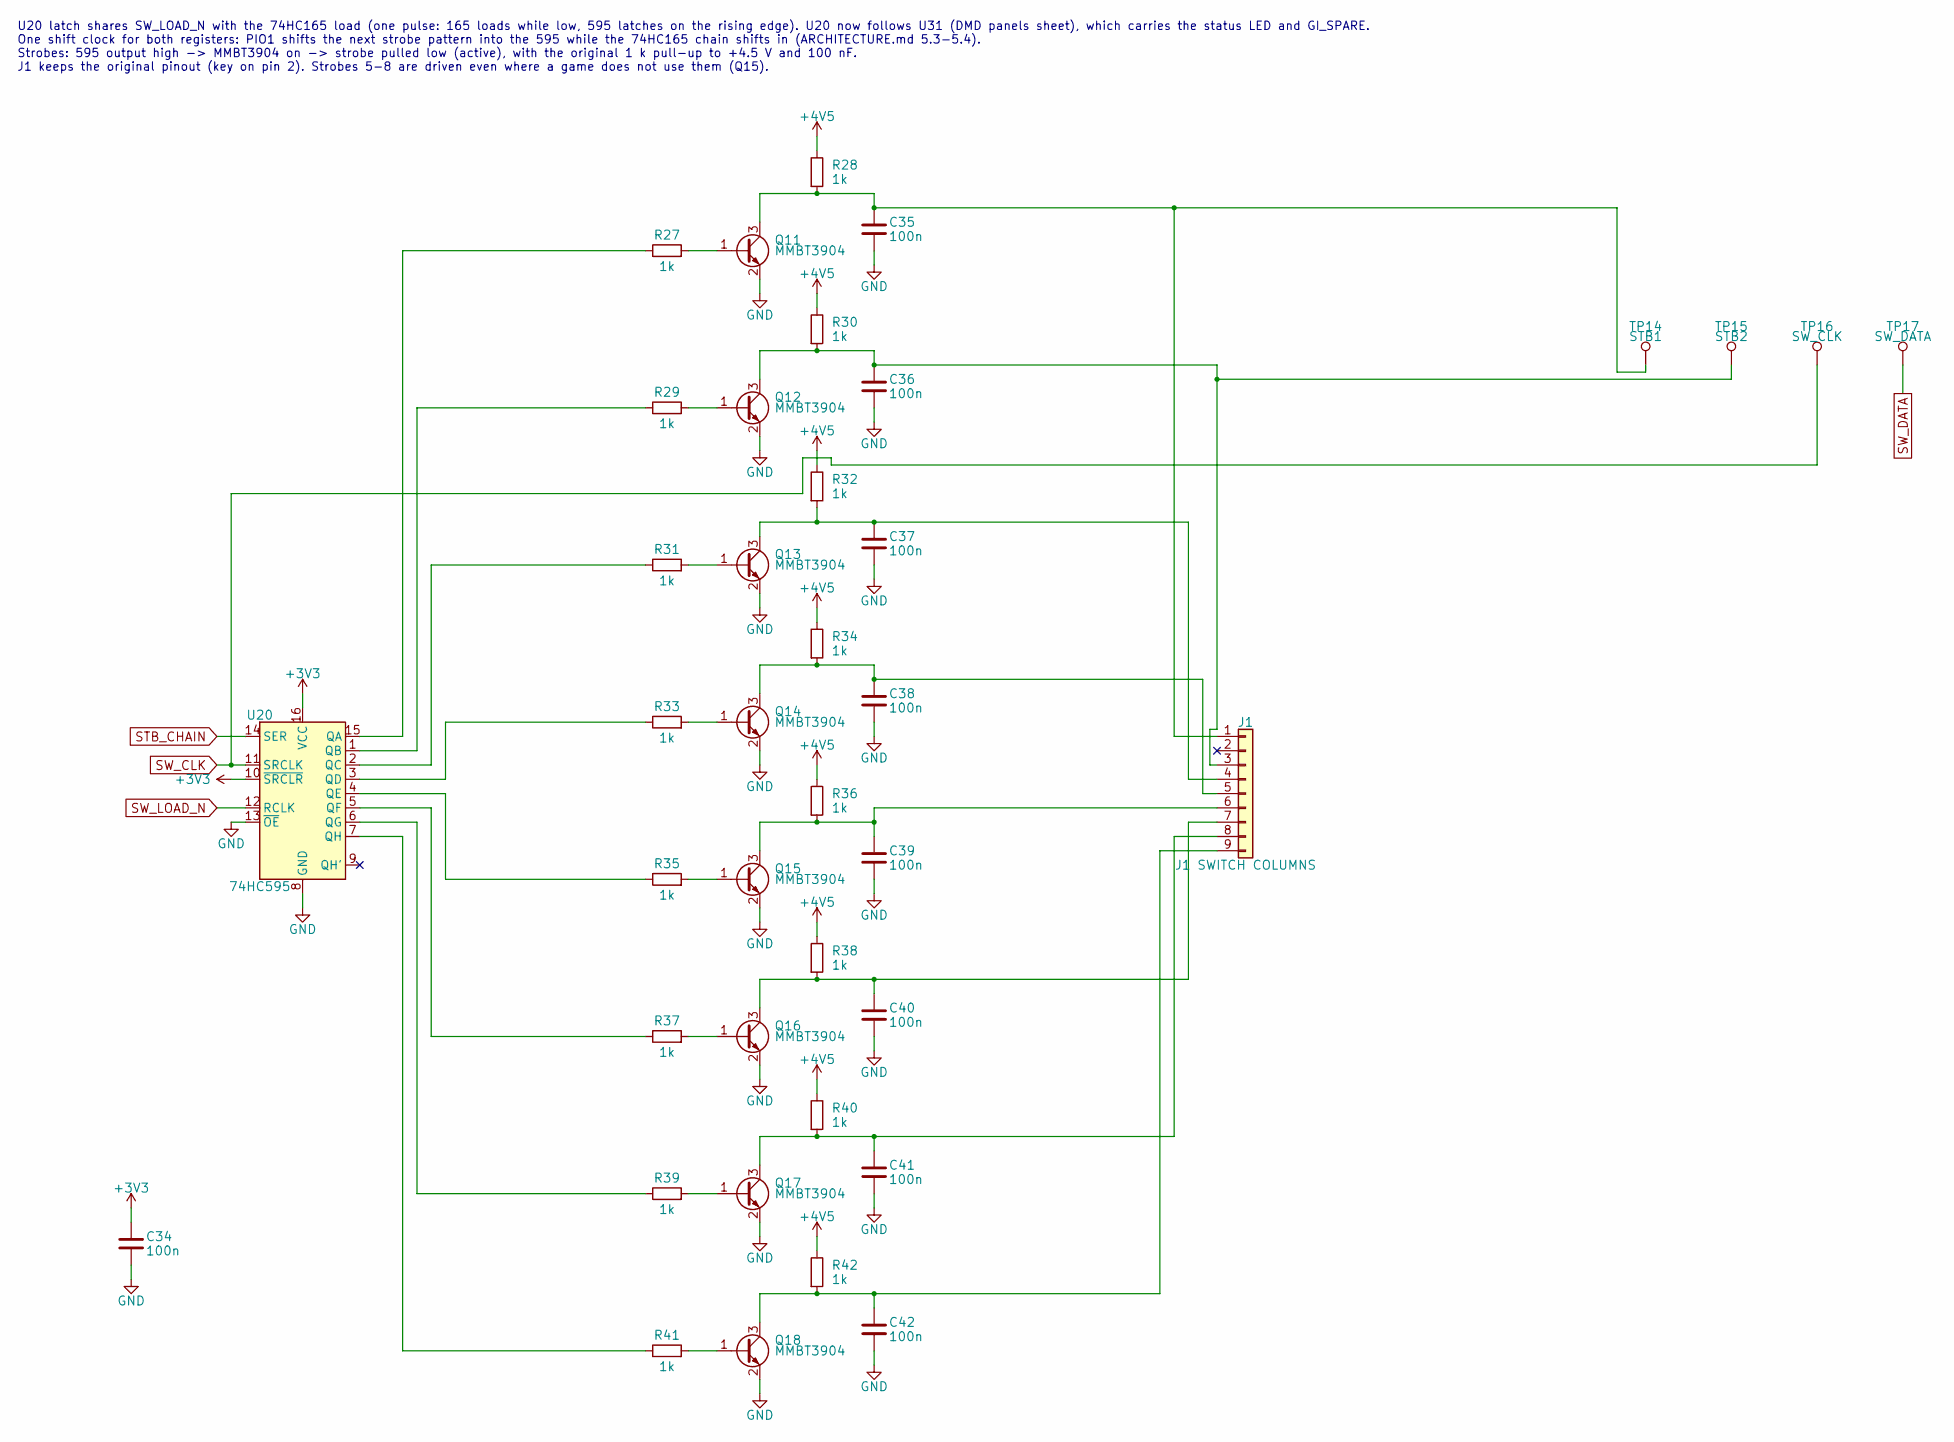
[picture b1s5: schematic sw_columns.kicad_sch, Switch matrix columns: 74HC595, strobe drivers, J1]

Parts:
C34, C35, C36, C37, C38, C39, C40, C41, C42: 100n; C_0603_1608Metric
J1: J1 SWITCH COLUMNS; Molex_KK-396_A-41791-0009_1x09_P3.96mm_Vertical
Q11, Q12, Q13, Q14, Q15, Q16, Q17, Q18: MMBT3904; SOT-23
R27, R28, R29, R30, R31, R32, R33, R35, R37, R38, R39, R40, R42: 1k; R_0603_1608Metric
R34, R36, R41: 1k; R_0805_2012Metric
TP14: STB1; TestPoint_Pad_D1.5mm
TP15: STB2; TestPoint_Pad_D1.5mm
TP16: SW_CLK; TestPoint_Pad_D1.5mm
TP17: SW_DATA; TestPoint_Pad_D1.5mm
U20: 74HC595; SOIC-16_3.9x9.9mm_P1.27mm

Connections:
+3V3: C34.1, U20.10 (~SRCLR), U20.16 (VCC); also elsewhere on the board
+4V5: R28.1, R30.1, R32.1, R34.1, R36.1, R38.1, R40.1, R42.1; also elsewhere on the board
GND: C34.2, C35.2, C36.2, C37.2, C38.2, C39.2, C40.2, C41.2, C42.2, Q11.2 (E), Q12.2 (E), Q13.2 (E), Q14.2 (E), Q15.2 (E), Q16.2 (E), Q17.2 (E), Q18.2 (E), U20.8 (GND), U20.13 (~OE); also elsewhere on the board
unnamed: C35.1, J1.1, Q11.3 (C), R28.2, TP14.1
unnamed: C36.1, J1.3, Q12.3 (C), R30.2, TP15.1
unnamed: C37.1, J1.4, Q13.3 (C), R32.2
unnamed: C38.1, J1.5, Q14.3 (C), R34.2
unnamed: C39.1, J1.6, Q15.3 (C), R36.2
unnamed: C40.1, J1.7, Q16.3 (C), R38.2
unnamed: C41.1, J1.8, Q17.3 (C), R40.2
unnamed: C42.1, J1.9, Q18.3 (C), R42.2
unnamed: Q11.1 (B), R27.2
unnamed: Q12.1 (B), R29.2
unnamed: Q13.1 (B), R31.2
unnamed: Q14.1 (B), R33.2
unnamed: Q15.1 (B), R35.2
unnamed: Q16.1 (B), R37.2
unnamed: Q17.1 (B), R39.2
unnamed: Q18.1 (B), R41.2
unnamed: R27.1, U20.15 (QA)
unnamed: R29.1, U20.1 (QB)
unnamed: R31.1, U20.2 (QC)
unnamed: R33.1, U20.3 (QD)
unnamed: R35.1, U20.4 (QE)
unnamed: R37.1, U20.5 (QF)
unnamed: R39.1, U20.6 (QG)
unnamed: R41.1, U20.7 (QH)
STB_CHAIN: U20.14 (SER); also elsewhere on the board
SW_CLK: TP16.1, U20.11 (SRCLK); also elsewhere on the board
SW_DATA: TP17.1; also elsewhere on the board
SW_LOAD_N: U20.12 (RCLK); also elsewhere on the board

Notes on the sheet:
U20 latch shares SW_LOAD_N with the 74HC165 load (one pulse: 165 loads while low, 595 latches on the rising edge). U20 now follows U31 (DMD panels sheet), which carries the status LED and GI_SPARE. One shift clock for both registers: PIO1 shifts the next strobe pattern into the 595 while the 74HC16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

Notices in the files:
hardware/kicad/sam_cpu/audio.kicad_sch:
Stern SAM CPU PPUC (CERN-OHL-S v2)
